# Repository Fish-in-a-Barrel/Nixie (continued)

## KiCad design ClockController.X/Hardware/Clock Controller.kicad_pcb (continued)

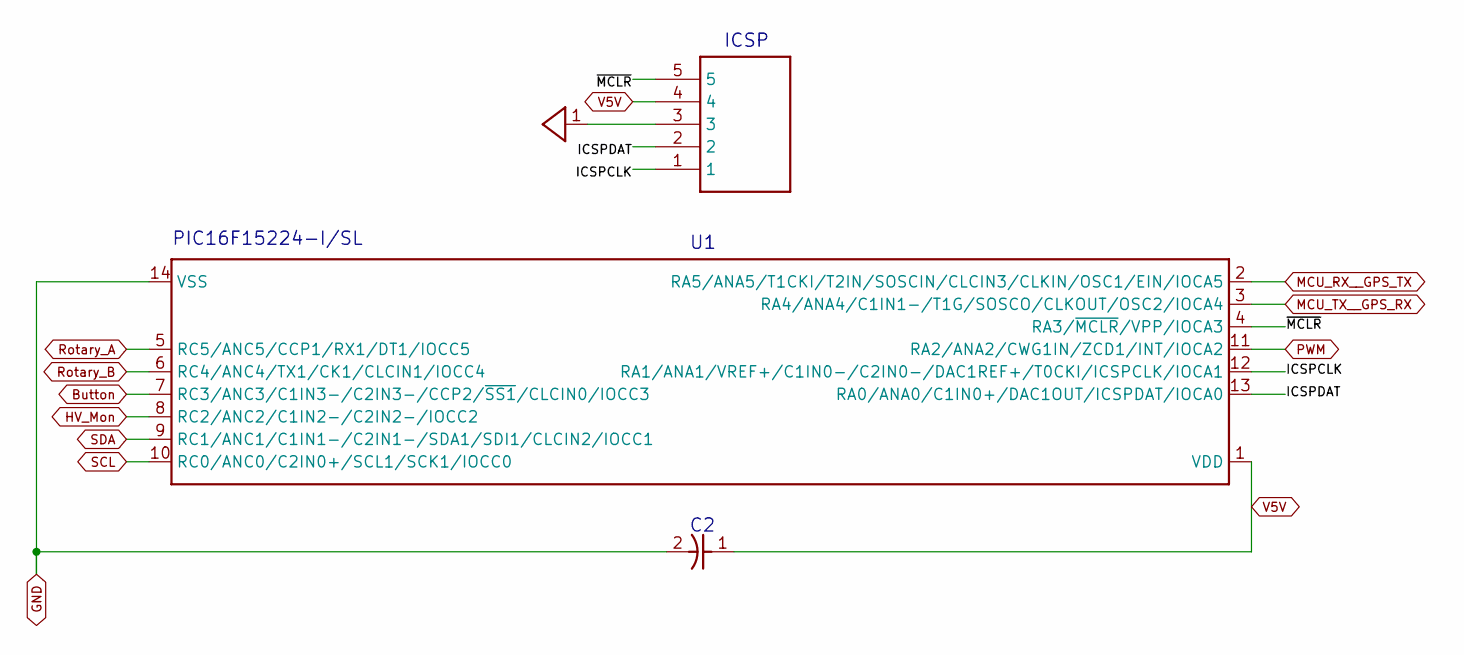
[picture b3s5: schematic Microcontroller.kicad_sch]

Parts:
C2: 100nF; C_0805_2012Metric
ICSP0: PPPC051LGBN-RC; PinSocket_1x05_P2.54mm_Horizontal
U1: PIC16F15224-I/SL; SOIC14P127_869X599X175L84X42N

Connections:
/Microcontroller/ICSPCLK: ICSP0.1, U1.12 (RA1/ANA1/VREF+/C1IN0-/C2IN0-/DAC1REF+/T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)
/Microcontroller/ICSPDAT: ICSP0.2, U1.13 (RA0/ANA0/C1IN0+/DAC1OUT/ICSPDAT/IOCA0)
/Microcontroller/~MCLR: ICSP0.5, U1.4 (RA3/~MCLR/VPP/IOCA3)
Button: U1.7 (RC3/ANC3/C1IN3-/C2IN3-/CCP2/~SS1/CLCIN0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); also elsewhere on the board
GND: C2.2, ICSP0.3, U1.14 (VSS); also elsewhere on the board
HV_Mon: U1.8 (RC2/ANC2/C1IN2-/C2IN2-/IOCC2); also elsewhere on the board
MCU_RX__GPS_TX: U1.2 (RA5/ANA5/T1CKI/T2IN/SOSCIN/CLCIN3/CLKIN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); also elsewhere on the board
MCU_TX__GPS_RX: U1.3 (RA4/ANA4/C1IN1-/T1G/SOSCO/CLKOUT/OSC2/I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); also elsewhere on the board
PWM: U1.11 (RA2/ANA2/CWG1IN/ZCD1/INT/IOCA2); also elsewhere on the board
Rotary_A: U1.5 (RC5/ANC5/CCP1/RX1/DT1/IOCC5); also elsewhere on the board
Rotary_B: U1.6 (RC4/ANC4/TX1/CK1/CLCIN1/IOCC4); also elsewhere on the board
SCL: U1.10 (RC0/ANC0/C2IN0+/SCL1/SCK1/IOCC0); also elsewhere on the board
SDA: U1.9 (RC1/ANC1/C1IN1-/C2IN1-/SDA1/SDI1/CLCIN2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); also elsewhere on the board
V5V: C2.1, ICSP0.4, U1.1 (VDD); also elsewhere on the board

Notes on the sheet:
PIC16F15224-I/SL
ICSP

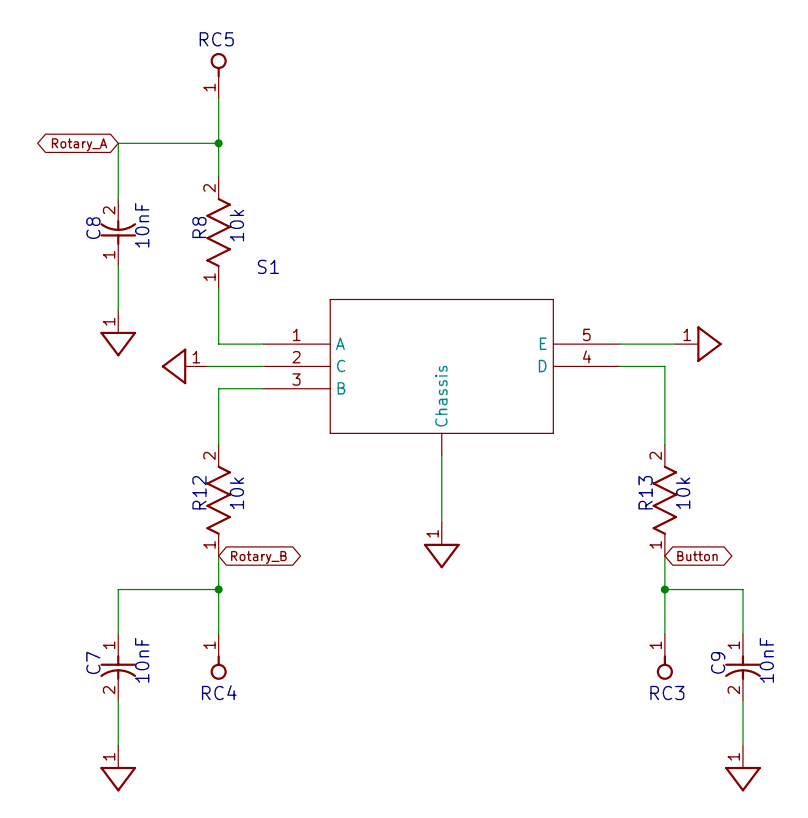
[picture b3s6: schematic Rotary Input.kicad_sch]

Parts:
C7, C8, C9: 10nF; C_0603_1608Metric
R8, R12, R13: 10k; R_0603_1608Metric
S1: PEC11S-929K-S0015

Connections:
Button: C9.1, R13.1; also elsewhere on the board
GND: C7.2, C8.1, C9.2, S1.2 (C), S1.5 (E), S1.10 (Chassis); also elsewhere on the board
unnamed: R8.1, S1.1 (A)
unnamed: R12.2, S1.3 (B)
unnamed: R13.2, S1.4 (D)
Rotary_A: C8.2, R8.2; also elsewhere on the board
Rotary_B: C7.1, R12.1; also elsewhere on the board

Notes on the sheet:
10k
10nF
R12
RC5
RC3
R13
RC4

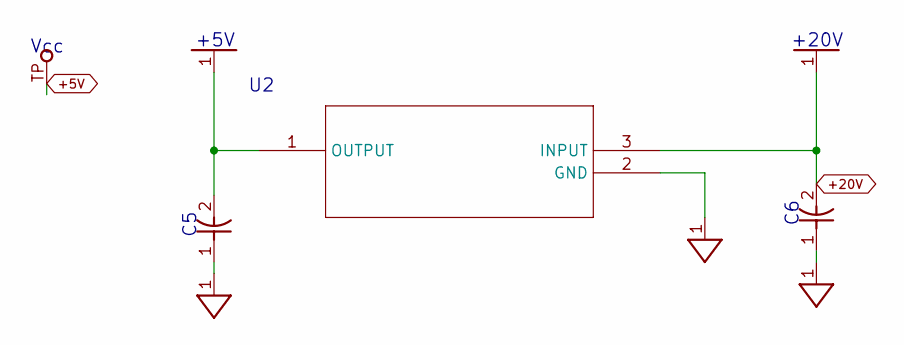
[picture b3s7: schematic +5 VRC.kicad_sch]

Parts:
C5, C6: 100nF; C_0805_2012Metric
U2: AS78L05RTR-E1; SOT-89-3
Vcc0: Most Density; TP_1.25MM

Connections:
+5V: C5.2, U2.1 (OUTPUT), Vcc0.TP; also elsewhere on the board
+20V: C6.2, U2.3 (INPUT); also elsewhere on the board
GND: C5.1, C6.1, U2.2 (GND); also elsewhere on the board

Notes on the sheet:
+20V
Vcc
+5V

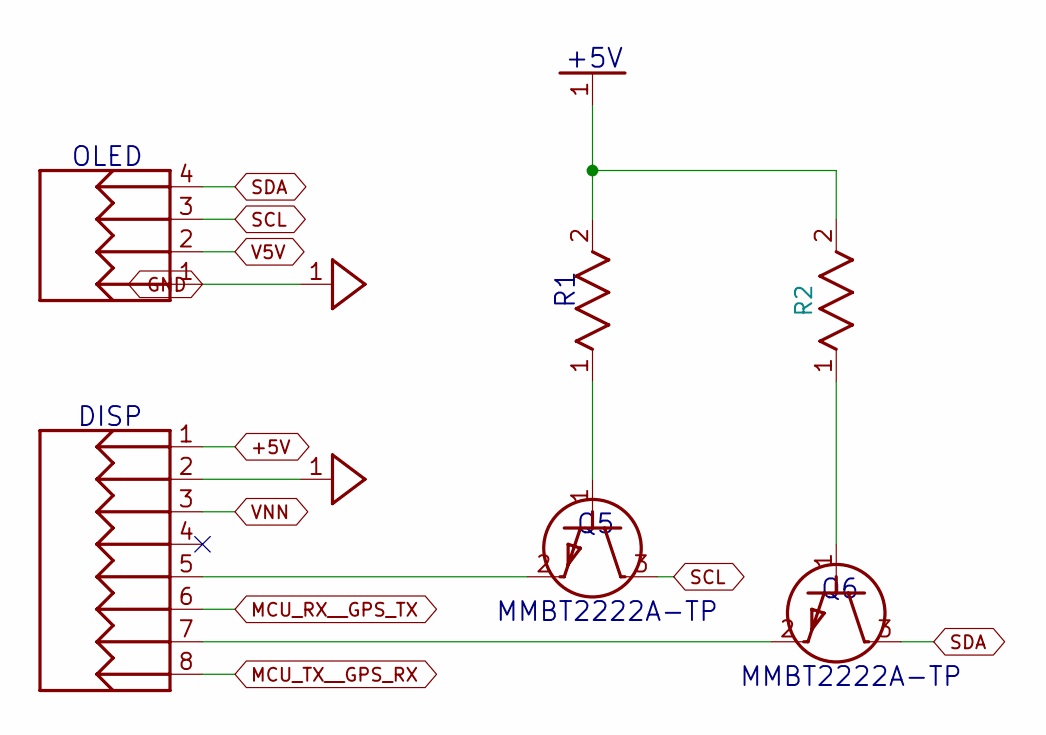
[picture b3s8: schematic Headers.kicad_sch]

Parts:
DISP0: HDR-2X4; PinHeader_2x04_P2.54mm_Vertical
OLED0: HDR-1X4; SSD1306 0.91 128x32 OLED
Q5, Q6: MMBT2222A-TP; SOT-23
R1, R2: 2.2k; R_0603_1608Metric

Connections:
+5V: DISP0.1, R1.2, R2.2; also elsewhere on the board
GND: DISP0.2, OLED0.1; also elsewhere on the board
MCU_RX__GPS_TX: DISP0.6; also elsewhere on the board
MCU_TX__GPS_RX: DISP0.8; also elsewhere on the board
unnamed: DISP0.5, Q5.2 (E)
unnamed: DISP0.7, Q6.2 (E)
unnamed: Q5.1 (B), R1.1
unnamed: Q6.1 (B), R2.1
SCL: OLED0.3, Q5.3 (C); also elsewhere on the board
SDA: OLED0.4, Q6.3 (C); also elsewhere on the board
V5V: OLED0.2; also elsewhere on the board
VNN: DISP0.3; also elsewhere on the board

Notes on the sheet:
DISP
OLED
+5V
MMBT2222A-TP

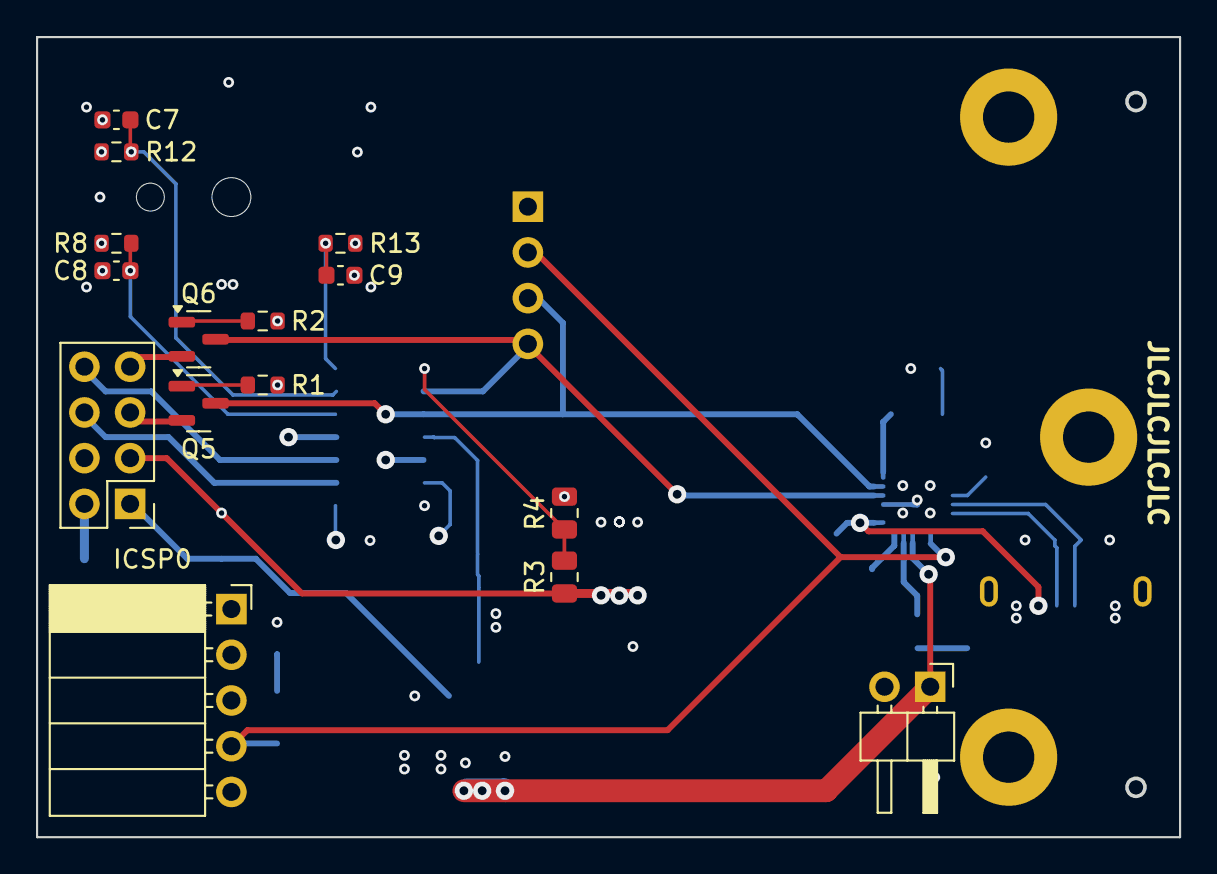
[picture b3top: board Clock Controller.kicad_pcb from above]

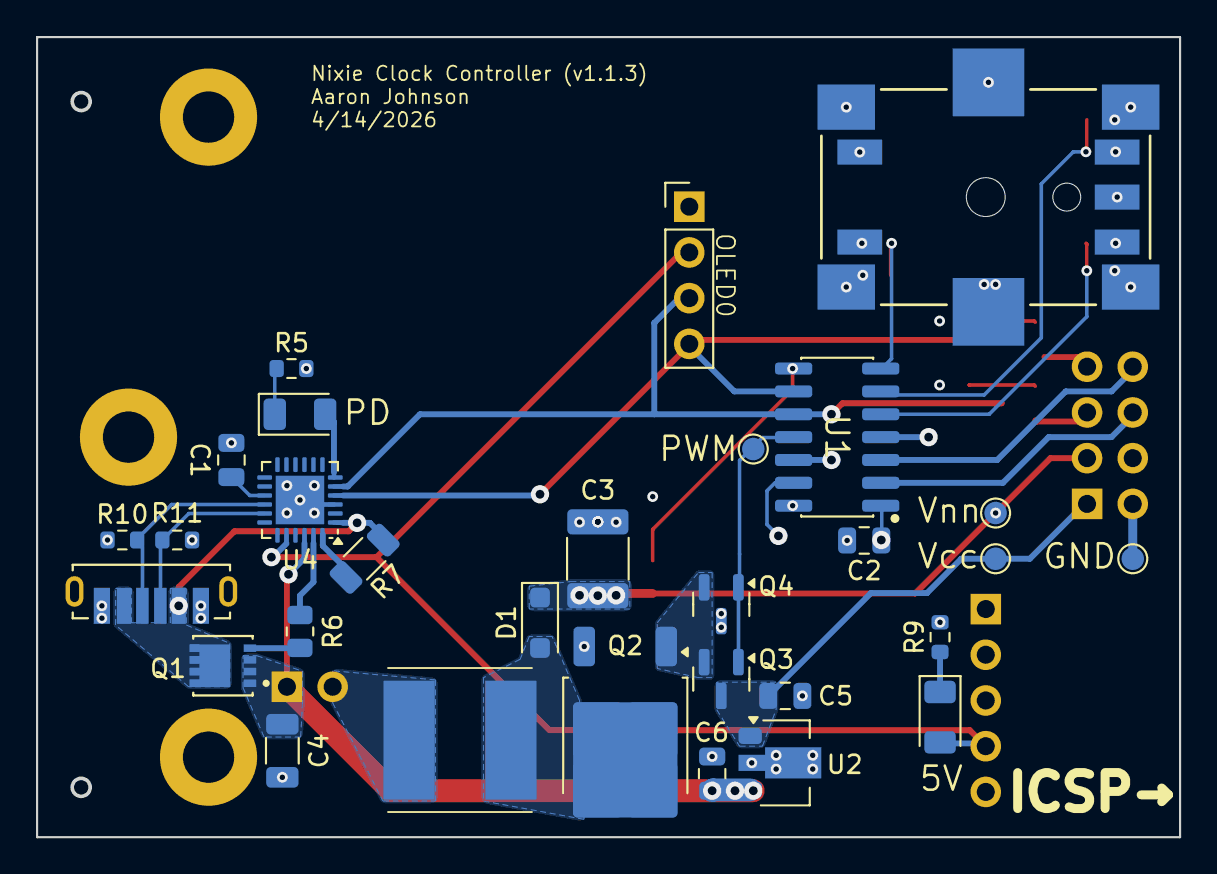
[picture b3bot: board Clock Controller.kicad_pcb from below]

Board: 4 copper layers, 63.4 x 44.4 mm, 48 parts (30 on the bottom side), 37 nets.

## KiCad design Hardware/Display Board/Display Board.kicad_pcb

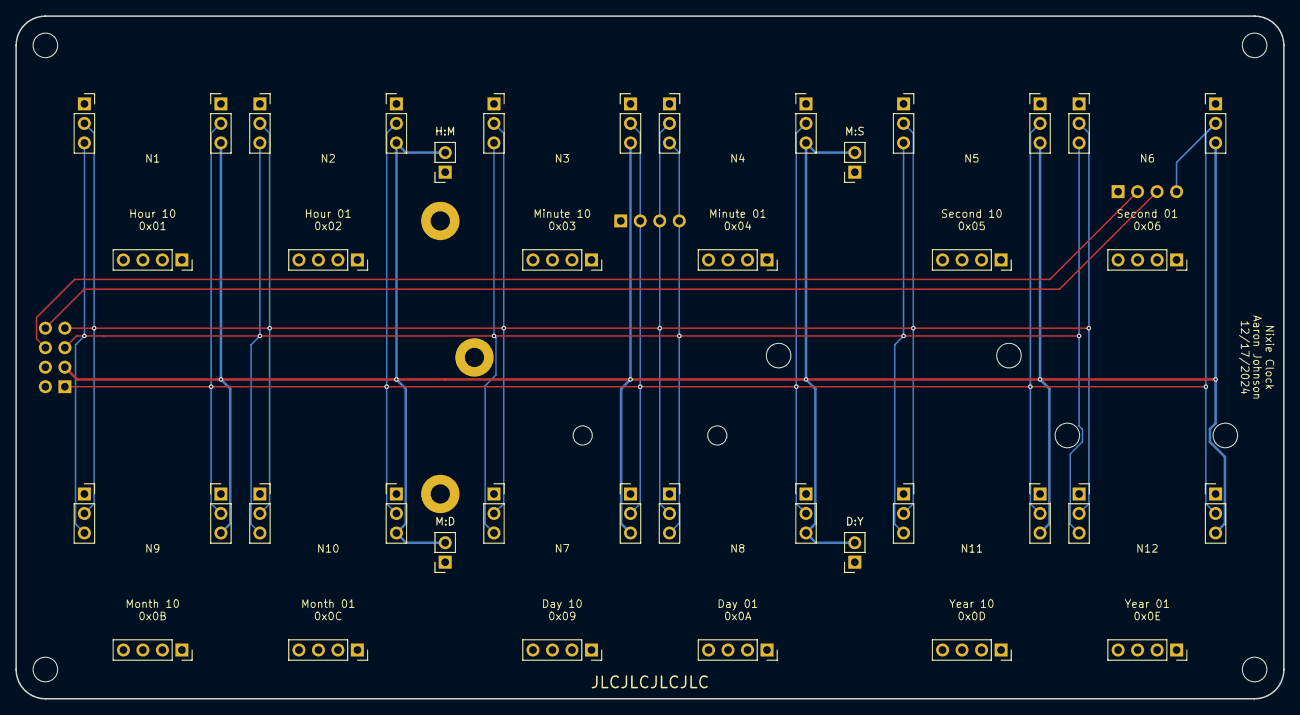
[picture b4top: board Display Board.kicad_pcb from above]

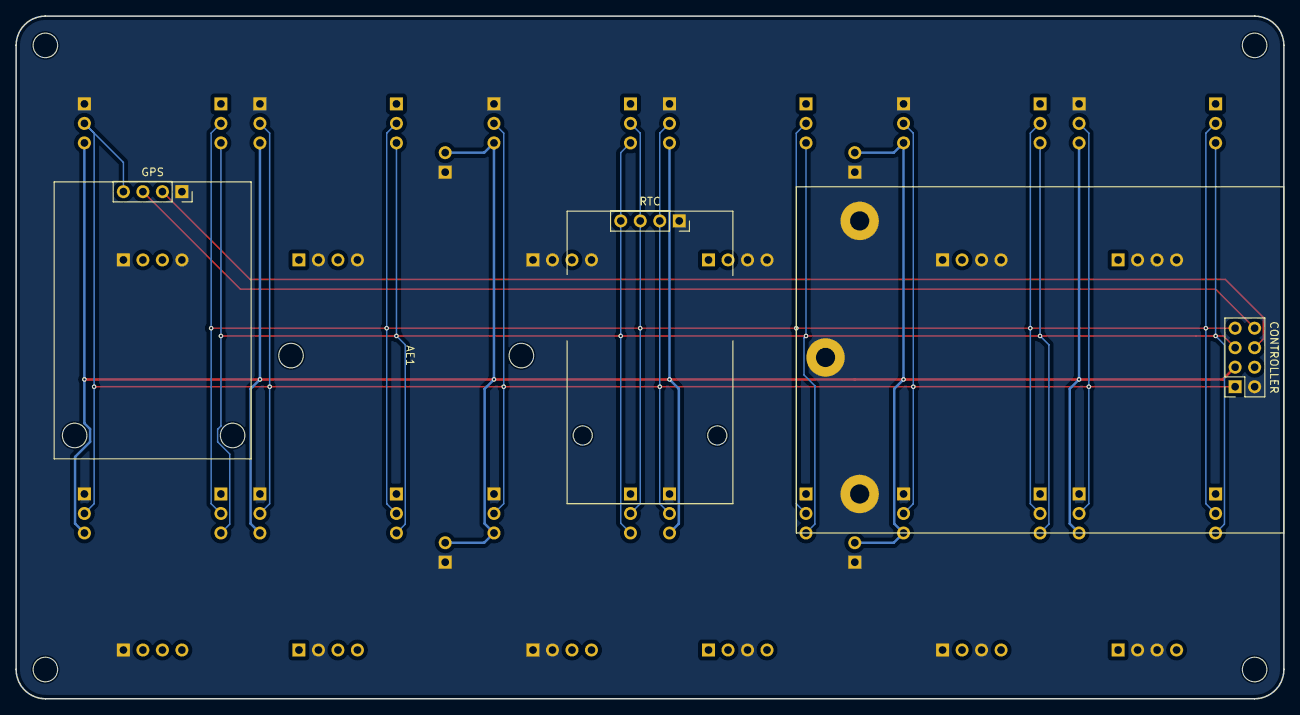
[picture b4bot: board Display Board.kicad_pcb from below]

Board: 2 copper layers, 165.1 x 88.9 mm, 31 parts (4 on the bottom side), 7 nets.

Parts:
AE1: GPS; GPS Antenna Holder
H1, H4, H7: MountingHole_Pad; MountingHole_2.5mm_Pad
H2, H5: MountingHole; MountingHole_2.5mm
H3, H6, H8, H9, H10, H11: MountingHole; MountingHole_3.2mm_M3
J1: GPS; PinSocket_1x04_P2.54mm_Vertical
J2: RTC; PinSocket_1x04_P2.54mm_Vertical
J3: CONTROLLER; PinSocket_2x04_P2.54mm_Vertical
J4: H:M; PinSocket_1x02_P2.54mm_Vertical
J5: M:D; PinSocket_1x02_P2.54mm_Vertical
J6: M:S; PinSocket_1x02_P2.54mm_Vertical
J7: D:Y; PinSocket_1x02_P2.54mm_Vertical
N1, N2, N3, N4, N5, N6, N7, N8, N9, N10, N11, N12: Nixie Driver V2

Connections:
GND: H1.1, H4.1, H7.1, J1.1, J2.1, J3.2, J4.1, J5.1, J6.1, J7.1, N1.4 (ADDR3), N1.5 (ADDR2), N1.6 (ADDR1), N1.10 (GND), N2.4 (ADDR3), N2.5 (ADDR2), N2.7 (ADDR0), N2.10 (GND), N3.4 (ADDR3), N3.5 (ADDR2), N3.10 (GND), N4.4 (ADDR3), N4.6 (ADDR1), N4.7 (ADDR0), N4.10 (GND), N5.4 (ADDR3), N5.6 (ADDR1), N5.10 (GND), N6.4 (ADDR3), N6.7 (ADDR0), N6.10 (GND), N7.5 (ADDR2), N7.10 (GND), N8.6 (ADDR1), N8.7 (ADDR0), N8.10 (GND), N9.5 (ADDR2), N9.6 (ADDR1), N9.10 (GND), N10.5 (ADDR2), N10.7 (ADDR0), N10.10 (GND), N11.6 (ADDR1), N11.10 (GND), N12.7 (ADDR0), N12.10 (GND)
MCU RX / GPS TX: J1.2, J3.6
MCU TX / GPS RX: J1.3, J3.8
SCL: J2.4, J3.5, N1.3 (SCL), N2.3 (SCL), N3.3 (SCL), N4.3 (SCL), N5.3 (SCL), N6.3 (SCL), N7.3 (SCL), N8.3 (SCL), N9.3 (SCL), N10.3 (SCL), N11.3 (SCL), N12.3 (SCL)
SDA: J2.3, J3.7, N1.2 (SDA), N2.2 (SDA), N3.2 (SDA), N4.2 (SDA), N5.2 (SDA), N6.2 (SDA), N7.2 (SDA), N8.2 (SDA), N9.2 (SDA), N10.2 (SDA), N11.2 (SDA), N12.2 (SDA)
Vdd: J1.4, J2.2, J3.1, N1.9 (Vdd), N2.9 (Vdd), N3.9 (Vdd), N4.9 (Vdd), N5.9 (Vdd), N6.9 (Vdd), N7.9 (Vdd), N8.9 (Vdd), N9.9 (Vdd), N10.9 (Vdd), N11.9 (Vdd), N12.9 (Vdd)
Vnn: J3.3, J4.2, J5.2, J6.2, J7.2, N1.8 (Vnn), N2.8 (Vnn), N3.8 (Vnn), N4.8 (Vnn), N5.8 (Vnn), N6.8 (Vnn), N7.8 (Vnn), N8.8 (Vnn), N9.8 (Vnn), N10.8 (Vnn), N11.8 (Vnn), N12.8 (Vnn)

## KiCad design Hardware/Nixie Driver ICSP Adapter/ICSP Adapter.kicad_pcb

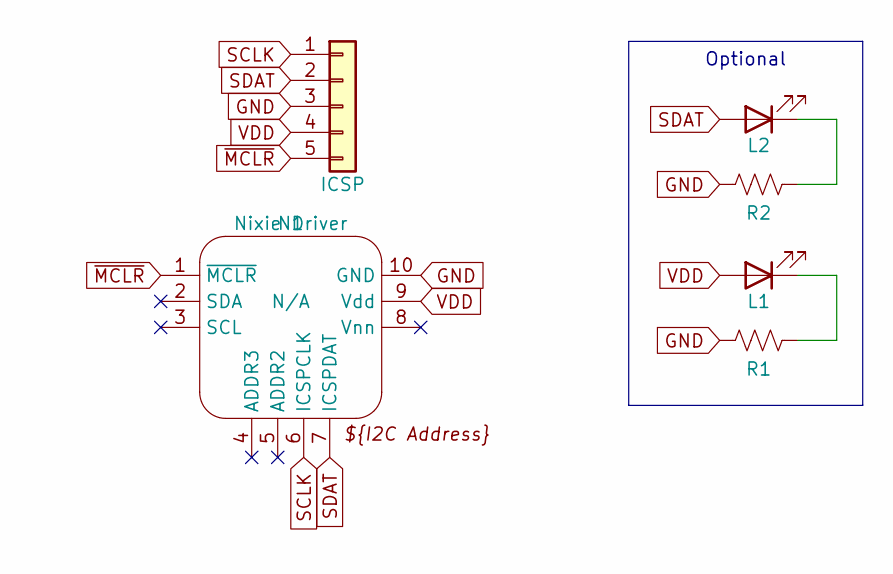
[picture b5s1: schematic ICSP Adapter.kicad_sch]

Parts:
J1: ICSP; PinHeader_1x05_P2.54mm_Horizontal
L1: PWR; LED_D5.0mm
L2: DAT; LED_D5.0mm
N1: Nixie Driver; Nixie Driver V2
R1, R2: 100; R_Axial_DIN0207_L6.3mm_D2.5mm_P7.62mm_Horizontal

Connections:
GND: J1.3, N1.10 (GND), R1.2, R2.2
unnamed: L1.1 (K), R1.1
unnamed: L2.1 (K), R2.1
SCLK: J1.1, N1.6 (ICSPCLK)
SDAT: J1.2, L2.2 (A), N1.7 (ICSPDAT)
VDD: J1.4, L1.2 (A), N1.9 (Vdd)
~MCLR: J1.5, N1.1 (~MCLR)

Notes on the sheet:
Optional

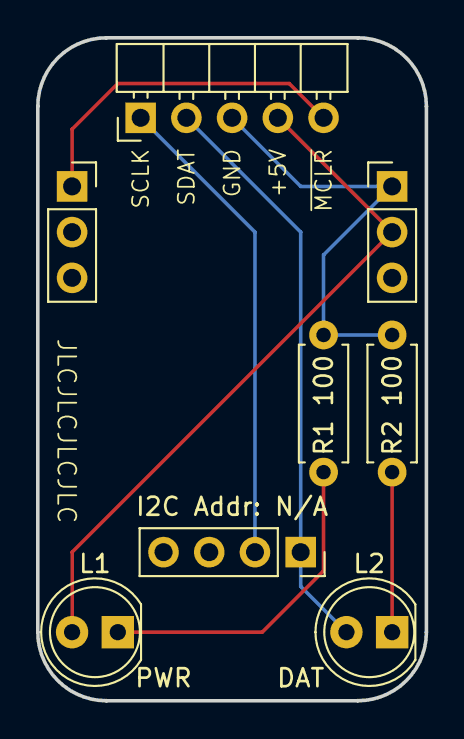
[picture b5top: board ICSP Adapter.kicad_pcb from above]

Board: 2 copper layers, 21.6 x 36.8 mm, 6 parts (0 on the bottom side), 7 nets.

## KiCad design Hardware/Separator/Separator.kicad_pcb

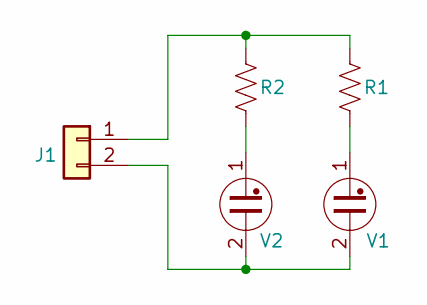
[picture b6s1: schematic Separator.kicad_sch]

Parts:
J1: Conn_01x02; PinHeader_1x02_P2.54mm_Vertical
R1, R2: 200k; R_1206_3216Metric
V1, V2: Lamp_Neon; INS-1

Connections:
unnamed: J1.1, R1.2, R2.2
unnamed: J1.2, V1.2, V2.2
unnamed: R1.1, V1.1
unnamed: R2.1, V2.1

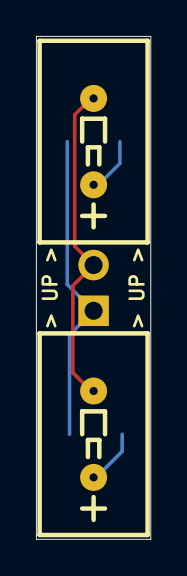
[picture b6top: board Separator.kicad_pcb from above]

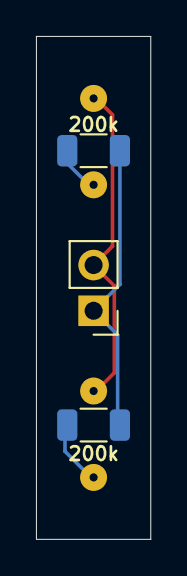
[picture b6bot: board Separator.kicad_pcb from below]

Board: 2 copper layers, 6.3 x 27.9 mm, 5 parts (3 on the bottom side), 4 nets.

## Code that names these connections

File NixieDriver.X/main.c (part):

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#include "pps_inputs.h"
#include "pps_outputs.h"

// The pin GPIO register for each cathode driver.
#define CATHODE_0_PIN RC3
#define CATHODE_9_PIN RC6
#define CATHODE_8_PIN RC7
#define CATHODE_7_PIN RB7
#define CATHODE_6_PIN RC4
#define CATHODE_5_PIN RC5
#define CATHODE_4_PIN RA4
#define CATHODE_3_PIN RA5
#define CATHODE_2_PIN RA2
#define CATHODE_1_PIN RC2
#define CATHODE_COMMA_PIN RB5

// The pin GPIO register for each address bit.
#define ADDRESS_PIN_0 RA0 // LSB
#define ADDRESS_PIN_1 RA1
#define ADDRESS_PIN_2 RC1
#define ADDRESS_PIN_3 RC0

// Note that this is shifted left by 1 bit for convenient use with the I2C registers.
#define I2C_ADDRESS (\
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
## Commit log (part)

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2023-12-16 Fixed DAT/CLK swapped on the connector
2023-12-23 Mostly works in actual use
2023-12-23 Consolidating docs
2023-12-23 Adding a delay before display init.
2023-12-23 Fixed incorrect pin read for button
2023-12-23 Some explanatory text for voltage divider
2023-12-23 Starting to tune the 180V control
2023-12-25 New MOSFET/Driver, completely new PCB
2023-12-25 Disabling LVP and MCLR on the assumption this lets drop the MCLR filter circuit
2023-12-30 Switched to 2x3 headers
2023-12-30 Added a dot cathode driver
2023-12-30 Dot driver refinement
2024-01-27 Refining driver
2024-01-28 Fixed dummy load
2024-01-28 Minor trace adjustments
2024-01-28 Removed switch cut-out
2024-01-28 Updated ICSP Nixie Adapter
2024-01-28 Fixed shorted trace
2024-01-28 Fixed DC connector polarity
2024-01-28 Silk and mask fixups
2024-01-28 Fixed missing +5V connection
2024-01-30 Production tweaks
2024-02-06 Moved power circuit to the left for USB C routing
2024-02-14 Fixed trace too close to pin pads. :(
2024-02-14 Fixed trace too close to pin pad. :(
2024-02-14 Fixed other bad trace.
2024-02-15 Increased PWR LED current limiting resistor
2024-02-16 Initial AP33772 test board design
2024-02-16 Switched to AP33772
2024-02-20 Updated for the rev B board
2024-02-20 Remove files that should not have been versioned
2024-02-27 Updated pin assignments
2024-02-27 Moved capacitor to MCU side
2024-02-27 Moved final SMD component to MCU side
2024-02-27 Updated silk screen
2024-02-28 Updated pins, added comma driver support
2024-02-28 Added toggling of the comma
2024-02-28 Layout tweaks.
2024-03-07 Started main boards
2024-03-07 Laid out Nixie interfaces
2024-03-07 Completed display board layout
2024-03-07 Fixed silk screen positions
2024-03-08 I don't know what I changed.
2024-03-08 Improved routing
2024-03-08 Positioning OLED and rotary
2024-03-08 More compact board
2024-03-08 Tweaked physical dimensions and fastener placement
2024-03-08 Moved vias away from MCU center
2024-03-10 Added hardware holes.
2024-03-10 Updated header parts
2024-03-10 I don't know what I did.
2024-03-10 Flipped display header pin assignments
2024-03-12 Updated main MOSFET part. Added more LEDS.
2024-03-12 Added test points
2024-03-12 Moved Q5 to a better location
2024-03-19 Fixed syntax error
2024-03-20 Placed headers for the separators
2024-03-30 Added separator lamp PCB
2024-03-30 Fixed GPS physical interface
2024-03-30 Fixed RTC group
2024-03-30 Moved daughter boards to center line
2024-03-30 Added drill holes for solder template alignment pins
2024-03-30 Added mounting holes for GPS antenna
2024-03-30 Added I2C addresses to silk screen
2024-03-30 Added separator assembly outlines
2024-03-30 Reduced separator board size
2024-03-30 Moved silkscreens now intersecting through holes
2024-03-30 Added solder template alignment features
2024-03-30 Updated copper pour
2024-03-30 Added label
2024-03-30 Fixed bad separator board design
2024-03-30 Added commend silk screens
2024-03-30 Fixed net collisions.
2024-03-30 Reordered nixie I2C addresses
2024-03-30 Removed unused power supply board.
2024-04-10 Added additional dimensions
2024-04-11 IDE update
2024-04-11 Switched to PIC 16F15224
2024-04-11 Don't update the nixies if the time hasn't changed
2024-04-11 Preprocessing GPS date/time strings
2024-04-11 Rename refactor
2024-04-11 Upped clock speed to 32 MHz
2024-04-11 Combined local time and DST adjustments
2024-04-11 Untrack some files.
2024-04-12 GPS Serial working
2024-04-12 Removed debug data structure
2024-04-13 Enable GPS/RTC sync
2024-04-13 Made day-of-week code more reusable
2024-04-13 AP33772 integration for USB PD working
2024-04-14 Copied/updated power control peripheral files
2024-04-14 Added boost converter control
    3725 (90.9%) ROM
2024-04-15 Use the WriteRead function instead of Write + Read
2024-04-15 Attempting to ruggedize the I2C
    ROM 3839, 93.7%
2024-04-15 First pass at button handling
2024-04-15 More compact button code
    ROM 4019
2024-04-15 Switch to PIC16F15225 for the extra ROM
2024-04-16 Fixed broken solder mask/paste on USB-C connector
2024-04-16 Moved the OLED for more conventional orientation.
2024-04-16 Fixing backwards ISEN resistor
2024-04-16 Less tortured routing
2024-04-16 Moved PD LED Back down by its source
2024-04-17 Added missing pull-downs on CC lines
2024-04-17 Starting pluggable conversion
2024-04-17 Moved USB connector closer to the header
2024-04-17 Smaller AP33772 board
2024-04-17 Tweaks
2024-04-20 Fixed Q5 pinout, updated USB PD
2024-04-20 Added missing resistors, fixed net names
2024-04-20 Added missing CCx resistors and fixed Q5 pins
2024-04-21 Simplified routing around USB
2024-04-21 Small silkscreen change.
2024-04-21 Flipped the OLED again.
2024-04-23 Added OLED support
2024-04-23 Config file stupidity.
2024-04-23 Fixed W/R bit not being set properly for callback writes.
2024-05-26 More robust AP33772 init
2024-05-26 Added the external VR
2024-05-26 Placed and routed VR
2024-05-26 Unsaved changes
2024-05-26 Update components
2024-05-26 Added filter caps to 5V VR
2024-05-26 Adjust component layout.
2024-05-26 Adjust component locations
2024-05-26 Adjust component placement.
2024-05-27 Fixed the ADC initialization
2024-06-08 Restart the AP33772 if it takes too long to get ready
2024-06-08 Added boost status display
2024-06-08 Fixed orientation of header
2024-06-08 Improved silkscreens.
2024-06-25 Rotated display, and fixed init
2024-06-25 Config updated
2024-06-25 Fixed reversed headers
2024-06-25 Move J2 to board edge
2024-06-25 Fixed level-shifting mosfet miswired
2024-06-25 Fixed MOSFET pins being mirrored in footprint
2024-06-25 Refining component placement
2024-06-25 DipTrace didn't actually save last time.
2024-06-26 Disconnect I2C devices with no power.
2024-06-26 Component position adjustment.
2024-06-26 Rotated RTC header back
2024-06-26 Added JLCPCB order # placeholder
2024-06-27 OLED function name refactor
2024-06-27 More display handling
2024-06-28 Using interrupts for switch handling
2024-06-28 Added a boost converter page
2024-06-29 Added USB PD page
2024-06-29 Started time zone / DST edit
2024-06-29 Scrolling of time zones.
2024-06-29 Save/Restore timezone
2024-06-29 Ignoring action that wakes up the screen
2024-06-29 Turn off the display with a click
2024-06-29 Added DST status indicator
2024-06-29 Fixed L2 optimization config
2024-06-30 Tweaked display board for JCL PCBA
2024-06-30 Unsaved changes.
2024-07-17 Add a config that does not use USB PD
2024-07-17 Addr pin start delay / NACK on data completion.
2024-08-04 Converted VBUS cut-off to horizontal header
2024-08-04 Removed unused hardware files
2024-08-16 I2C fixes, including processor speed increase
2024-08-16 Using some less obfuscated code
2024-08-27 Added doxygen comments
2024-08-27 Simplified OLED calls to fix stack overflow
2024-09-04 Fix the read-back handling
2024-10-15 Started converting controller to KiCad 8
2024-10-20 Cleaned up a bunch of labels
2024-10-20 Updated most footprints
2024-10-20 Aligned test points
2024-10-20 Deleted unused I2C pull-up resistors
2024-10-21 Fixed footprint issue with Q1
2024-10-21 Initial KiCad import of Nixie Driver
2024-10-21 Migration from DipTrace. Updated symbols and footprints.
2024-10-21 Board cleanup
2024-10-21 Deleted empty labels
2024-10-21 Updated silkscreens
2024-12-01 Fixed display switching off at startup
2024-12-01 Revert back to TMR2
    Using PWM3 wasn't triggering the ADC interrupts.
    It also doesn't seem to like running off TMR2 with no post-scaller
2024-12-01 Tuned ADC values
2024-12-02 Fixed OVP warning placement
2024-12-02 Preserving the voltage/ADC value when OVP trips
2024-12-03 Initial P-control setup
2024-12-14 Separator board in KiCad
    Added a second resistor because both lamps won't light simultaneously with one.
2024-12-14 Deleted old DipTrace files
2024-12-14 Converted ICSP adapter to KiCad
2024-12-14 Modified ICSP header footprint
2024-12-14 Rounded PCB corners
2024-12-16 DRC Exclusions
2024-12-16 Redesign for current limiting
2024-12-16 Optimized PCB layout
2024-12-17 drc updates
2024-12-17 Reduced resistor size to 0805
2024-12-17 Fixed stencil alignment holes.
2024-12-18 Starting Display Board in KiCad
2024-12-18 Components placed
2024-12-18 KiCad display board completed
2024-12-18 Prettying up the board a bit.
2024-12-18 Cleaned up the copper pour
2024-12-18 Rotated GPS module for better antenna routing
2024-12-18 Separated the grounds so the test harness will still work.
2024-12-25 Added holes for the antenna holder
2024-12-25 Removed obsolete documents folder
2025-01-14 Move resistor back to the anode
2025-01-15 Cleaned up traces.
2025-01-15 Upsized current-limiting resistor
2025-01-30 Fixed digits never illuminating
2025-02-01 Added small negative solder mask expansion to MCU
2025-02-02 Fixed comma inhibit logic
2025-02-02 ignore new temp/lock file
2025-02-04 Added Nixie Driver Tester hardware (incomplete)
2025-02-04 Replaced the MCU symbol
2025-02-04 4-layer PCB routed.
2025-02-04 Added Nixie headers
2025-02-04 Slight layout adjustment.
2025-02-04 Initial component layout.
2025-02-04 First reasonable layout.
2025-02-04 Status LEDs and switch labels
2025-02-04 One mounting hole
2025-02-04 Two mounting holes
2025-02-05 Major layout change to get the L out of the way
2025-02-05 Shrink the board a bit.
2025-02-05 Removed unused silk
2025-02-05 Cleaned up the net classes
2025-02-05 Clean up some silkscreen positions.
2025-02-05 V2 ICSP adapter
2025-02-06 Switched to custom OLED symbol/footprint
2025-02-06 Switched to custom nixie driver symbol/footprint
2025-02-06 Shrunk the board vertically
2025-02-06 Replace OLED mounting hole with slot
2025-02-06 Spread out components clustered by the on/off switch
2025-02-06 Replaced slot with rectangle
    The end points of the arcs and lines didn't match up in the OSH preview.
2025-02-07 Added some dimension markers.
2025-02-08 Fixed clearance issues
2025-02-08 Update clearances
2025-02-09 Updated Display Board to V2 Nixies
    The Antenna holder needs to be redesigned. Lots of silkscreen errors to fix.
2025-02-19 Fixed first command ignored if zero
2025-02-23 Simplify padding bits definitions
2025-02-23 Fixed OVP warning not turning off
2025-02-23 Re-enable screen time-out
2025-02-23 First time everything worked!
2025-02-23 Holding OVP symbol
2025-02-23 Fixed 12/24-hour RTC bit
2025-02-23 Enabling weak pull-ups on address pins
2025-02-23 Fixed section markers
2025-02-23 Remove unneeded weak pull-up code
2025-02-23 Squashed commit of the following:
    commit 2b46fe7b71221aaec37e9e0d3aee2aa990eb3e65
    Author: Fish-in-a-Barrel <aaron.m.johnson@gmail.com>
    Date: Sat Feb 22 19:06:52 2025 -0600
    Remove unused files
    commit 1bf26ed803d2ce20de53ef10f76724fbb63c3649
    Author: Fish-in-a-Barrel <aaron.m.johnson@gmail.com>
2025-03-06 Fixed address instability
    Weak pull-up not being enabled on address pins caused some Nixies to sometimes miss some address bits.
2025-09-14 readme
2025-09-14 Updated colors that are more readable on dark backgrounds
2025-09-14 Fixed 78L05 connection
2025-09-14 Update readme.md with video
2025-09-14 Update readme.md - Cropped video with tracking
2026-02-08 Update Kicad version.
2026-02-08 Removed imported objects
2026-02-09 Current-limiting-resistor for each driver
2026-02-09 Small layout tweaks.
2026-04-02 Replacing many thin traces with poured zones.
2026-04-02 Moved the VRM for shorter traces
2026-04-02 More zones
2026-04-04 Simplified I2C cutoff
2026-04-04 Moved C3
2026-04-04 Moved the VRM closer to the main load
2026-04-04 Cleanup of the silkscreens.
2026-04-04 Added stencil alignment holes
2026-04-04 Relocated the test points
2026-04-04 4-layer board
2026-04-05 Named all nets
2026-04-05 Fixed page numbers
2026-04-05 Added RTC and battery to schematic
2026-04-05 Added missing footprint assignment
2026-04-11 Fixed some broken 3d model references
2026-04-11 Updated some footprints
2026-04-12 Converting to single board layout
2026-04-15 Updated tools
2026-04-15 Updated version number on board
